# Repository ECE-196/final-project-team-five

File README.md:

# Final Project

[Website](https://eceunilock.wordpress.com)

[Poster](https://docs.google.com/presentation/d/16C1Z2XDyntSw6JHbOTtGmIsTxYupsFhoAjeBmQPg56s/edit?usp=sharing)

[Lock_V1](https://drive.google.com/file/d/1l9DyjJKeOXGftBQB_VL0KF6kT_iQgPzs/view?usp=sharing)

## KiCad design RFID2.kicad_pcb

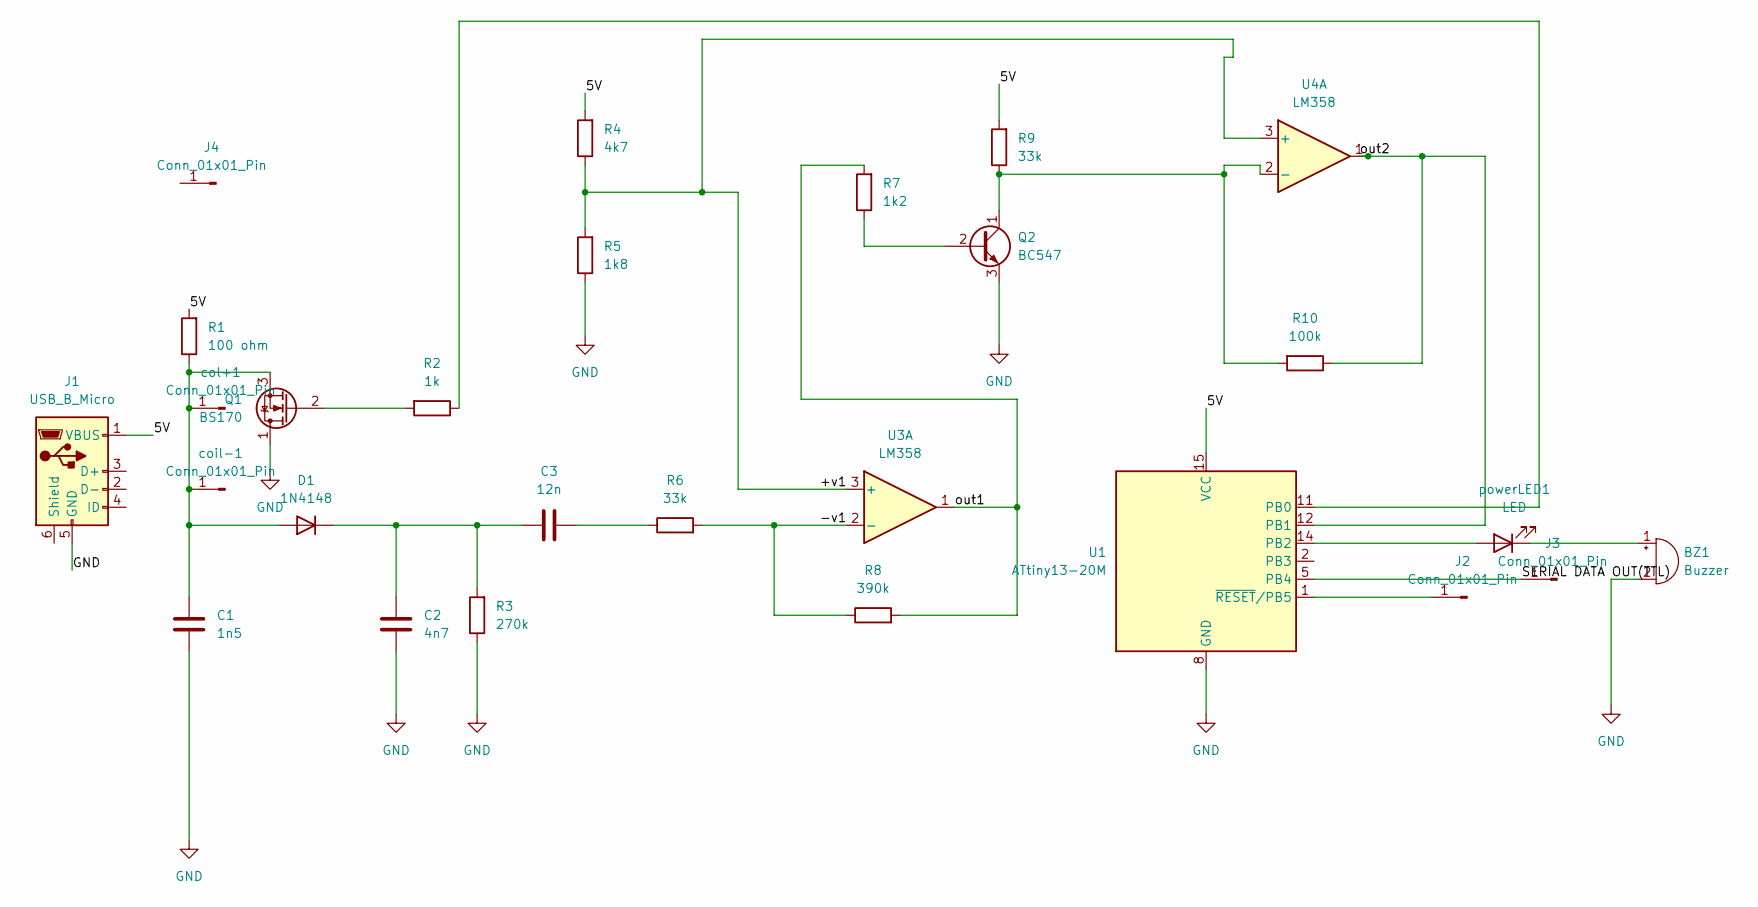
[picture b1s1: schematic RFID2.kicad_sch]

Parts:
BZ1: Buzzer; Buzzer_TDK_PS1240P02BT_D12.2mm_H6.5mm
C1: 1n5; C_0201_0603Metric
C2: 4n7; C_0201_0603Metric
C3: 12n; C_0201_0603Metric
D1: 1N4148; D_DO-35_SOD27_P7.62mm_Horizontal
J1: USB_B_Micro; USB_Micro-B_Amphenol_10103594-0001LF_Horizontal
J2, J3, J4: Conn_01x01_Pin; PinHeader_1x01_P1.00mm_Vertical
Q1: BS170; TO-92_Inline
Q2: BC547; TO-92_Inline
R1: 100 ohm; R_2512_6332Metric
R2: 1k; R_2512_6332Metric
R3: 270k; R_2512_6332Metric
R4: 4k7; R_2512_6332Metric
R5: 1k8; R_2512_6332Metric
R6, R9: 33k; R_2512_6332Metric
R7: 1k2; R_2512_6332Metric
R8: 390k; R_2512_6332Metric
R10: 100k; R_2512_6332Metric
U1: ATtiny13-20M; QFN-20-1EP_4x4mm_P0.5mm_EP2.6x2.6mm
U3, U4: LM358; DIP-8-16_W7.62mm
coil-1: Conn_01x01_Pin; PinHeader_1x01_P1.00mm_Vertical
col+1: Conn_01x01_Pin; PinHeader_1x01_P1.00mm_Vertical
powerLED1: LED; LED_2512_6332Metric

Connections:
/5V: J1.1 (VBUS), R1.2, R4.2, R9.2, U1.15 (VCC)
/+v1: R4.1, R5.2, U3.3 (+), U4.3 (+)
/-v1: R6.2, R8.1, U3.2 (-)
/SERIAL DATA OUT(TTL): J3.1, U1.5 (PB4)
/out1: R7.2, R8.2, U3.1
/out2: R10.1, U1.12 (PB1), U4.1
GND: BZ1.2 (-), C1.1, C2.1, J1.5 (GND), Q1.1 (D), Q2.3 (E), R3.1, R5.1, U1.8 (GND), U1.21 (GND)
unnamed: BZ1.1 (+), powerLED1.1 (K)
unnamed: C3.2, R6.1
unnamed: C1.2, D1.2 (A), Q1.3 (S), R1.1, coil-1.1, col+1.1
unnamed: C2.2, C3.1, D1.1 (K), R3.2
unnamed: J2.1, U1.1 (~RESET/PB5)
unnamed: Q1.2 (G), R2.2
unnamed: Q2.2 (B), R7.1
unnamed: Q2.1 (C), R9.1, R10.2, U4.2 (-)
unnamed: R2.1, U1.11 (PB0)
unnamed: U1.14 (PB2), powerLED1.2 (A)

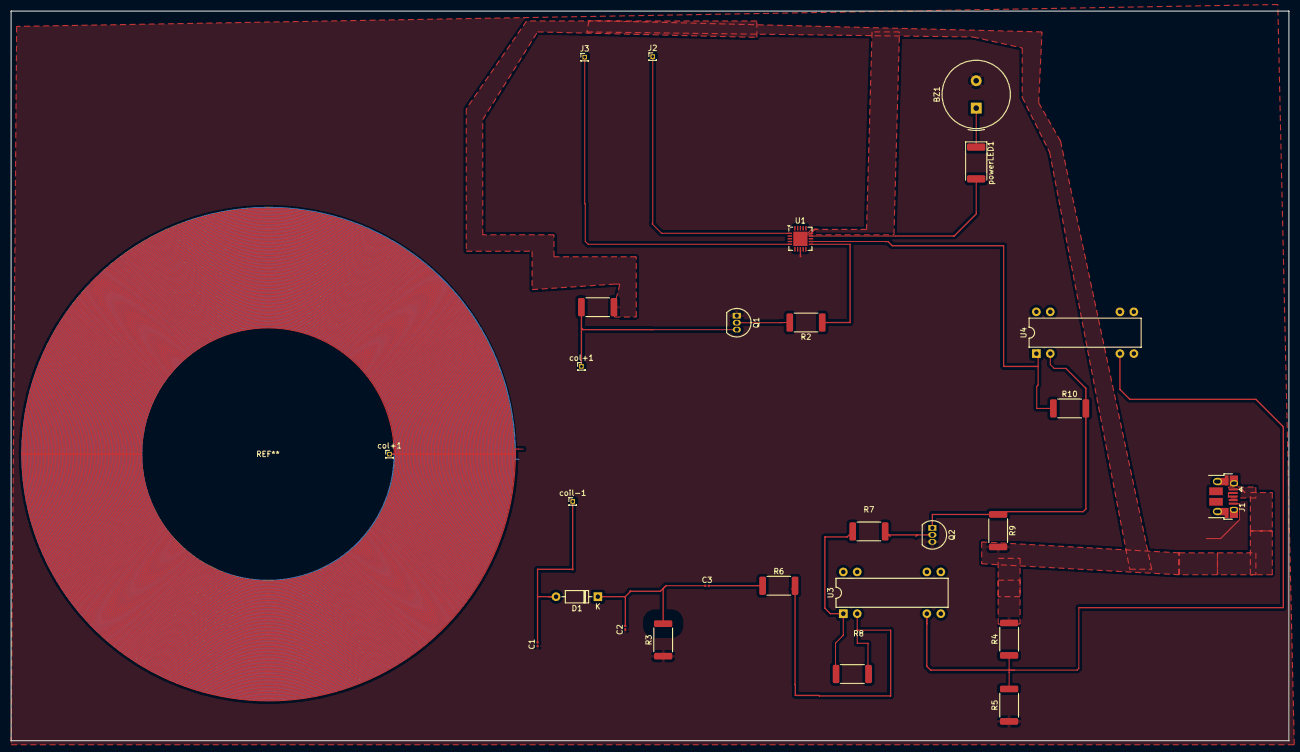
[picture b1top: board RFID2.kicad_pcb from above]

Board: 2 copper layers, 233.0 x 133.1 mm, 27 parts (0 on the bottom side), 17 nets.

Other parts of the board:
col+1#2: Conn_01x01_Pin; PinHeader_1x01_P1.00mm_Vertical

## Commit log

2024-10-29 pcb draft
2024-10-31 Upload Video Submission
2024-11-04 Create LOCK_V1.stl
    Version 1.0 of our locking mechanism.
2024-11-05 Corrections to V1 Lock
2024-11-05 Demo of Lock V1
2024-11-05 Remove File/Add Link
    https://drive.google.com/file/d/1l9DyjJKeOXGftBQB_VL0KF6kT_iQgPzs/view?usp=sharing
2024-11-06 pcb
    updated
2024-11-27 Initial Upload
    Code works last tested: Nov 25, 2024
2024-11-27 LockHub Class
    Moved ino code and create class
2024-11-27 Readjusted LockHub API
    Locking and unlocking methods no longer need a card. Card verification should be done by user implementation.
2024-11-27 Add error handling for uninitialized variables
    Added error handling for not having opening and closing angles set
2024-11-27 Reupdate Code
    Tested Nov 27.
